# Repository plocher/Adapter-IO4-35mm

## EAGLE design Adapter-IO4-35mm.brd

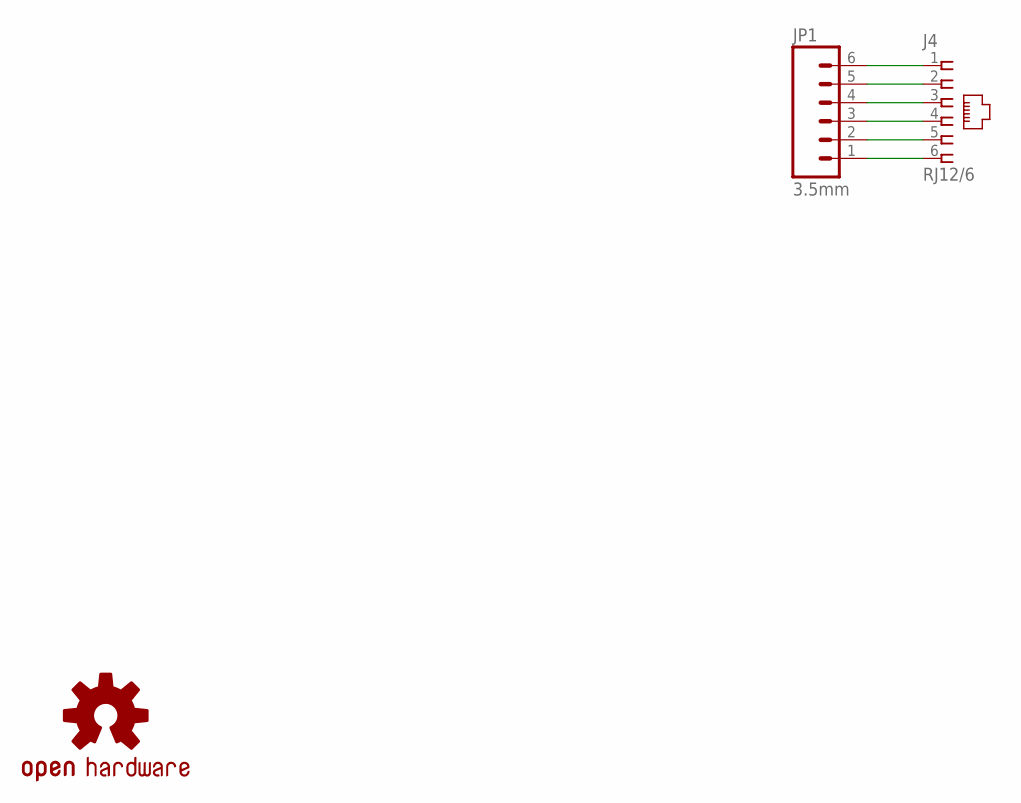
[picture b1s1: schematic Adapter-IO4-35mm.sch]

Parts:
J4: RJ12/6; RJ25-PANEL
JP1: 3.5mm; SCREWTERMINAL-3.5MM-6
U$1: OSHW; OSHW-LOGO-M

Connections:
GND: J4.6, JP1.1
IO1: J4.2, JP1.5
IO2: J4.3, JP1.4
IO3: J4.4, JP1.3
IO4: J4.5, JP1.2
VCC: J4.1, JP1.6

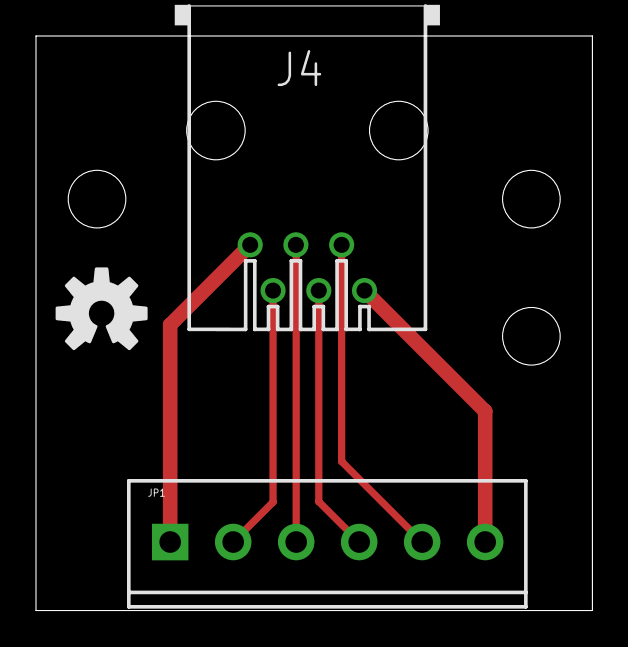
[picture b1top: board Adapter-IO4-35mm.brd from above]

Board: 2 copper layers, 30.9 x 31.9 mm, 3 parts (0 on the bottom side), 6 nets.

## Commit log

2019-12-09 added graphic
2020-05-04 updated tags
2020-10-05 added values for connectors
2020-10-06 normalized values

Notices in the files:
parts and their libraries:
SPCoast: http://freedomdefined.org/OSHW Creative Commons - Attribution - ShareAlike 3.0
